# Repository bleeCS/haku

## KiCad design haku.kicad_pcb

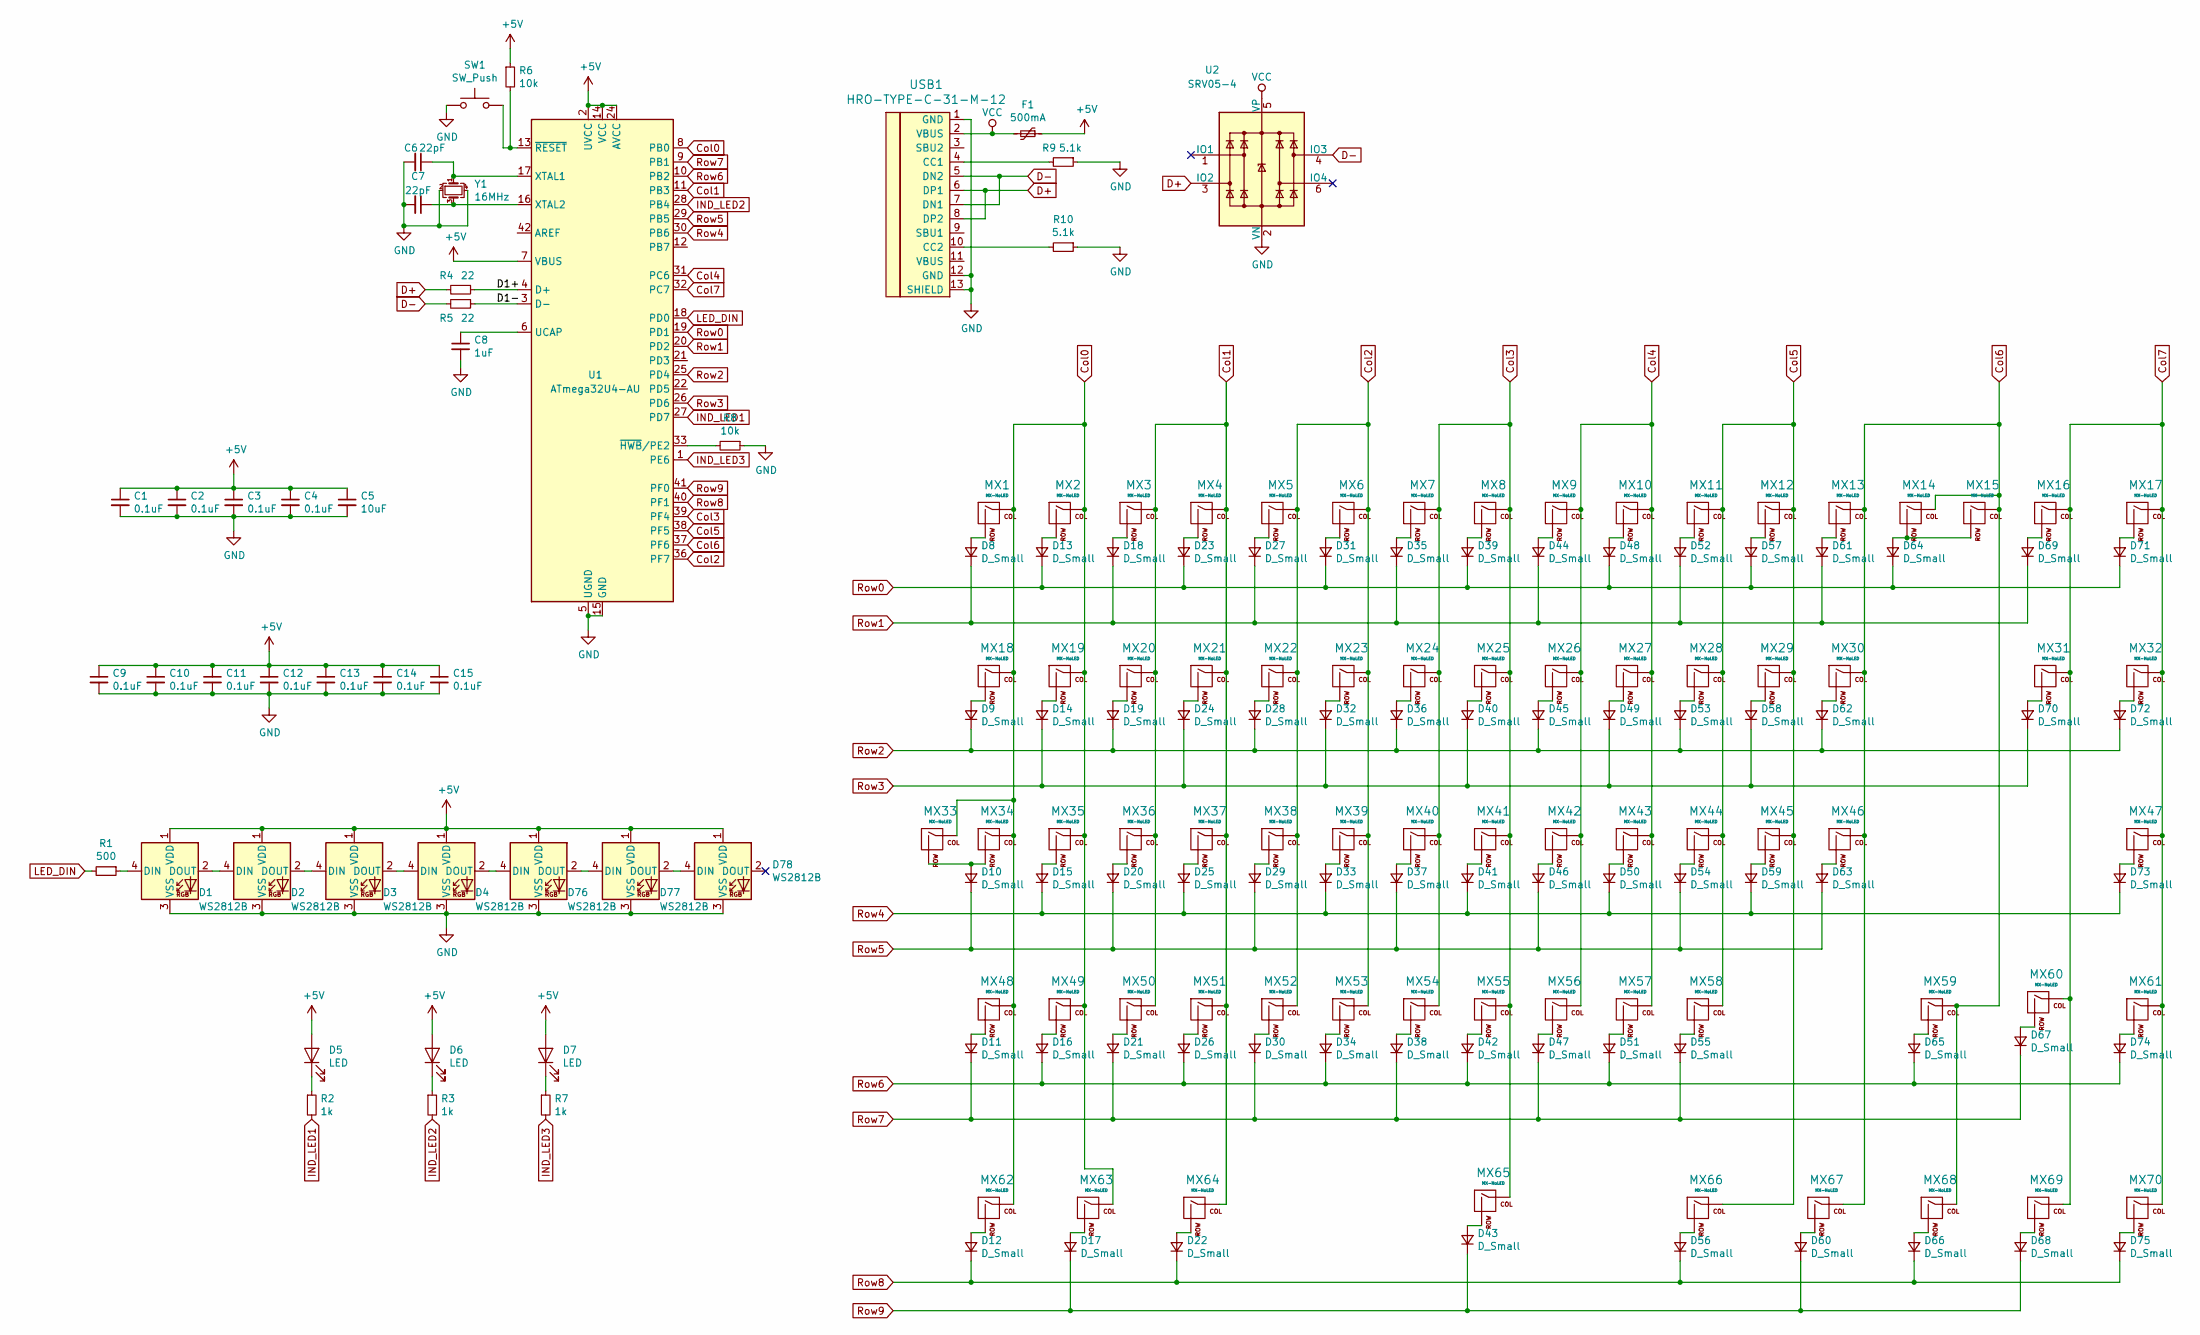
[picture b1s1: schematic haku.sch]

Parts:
C1, C2, C3, C4, C9, C10, C11, C12, C13, C14, C15: 0.1uF; C_0805_2012Metric
C5: 10uF; C_0805_2012Metric
C6, C7: 22pF; C_0805_2012Metric
C8: 1uF; C_0805_2012Metric
D1, D2, D3, D4, D76, D77, D78: WS2812B; LED_WS2812B_PLCC4_5.0x5.0mm_P3.2mm
D5, D6, D7: LED; LED_D3.0mm-Pretty
D8, D9, D10, D11, D12, D13, D14, D15, D16, D17, D18, D19, D20, D21, D22, D23, D24, D25, D26, D27, D28, D29, D30, D31, D32, D33, D34, D35, D36, D37, D38, D39, D40, D41, D42, D43, D44, D45, D46, D47, D48, D49, D50, D51, D52, D53, D54, D55, D56, D57, D58, D59, D60, D61, D62, D63, D64, D65, D66, D67, D68, D69, D70, D71, D72, D73, D74, D75: D_Small; D_SOD-123
F1: 500mA; Fuse_1206_3216Metric
MX1, MX2, MX3, MX4, MX5, MX6, MX7, MX8, MX9, MX10, MX11, MX12, MX13, MX14, MX16, MX17, MX19, MX20, MX21, MX22, MX23, MX24, MX25, MX26, MX27, MX28, MX29, MX30, MX32, MX35, MX36, MX37, MX38, MX39, MX40, MX41, MX42, MX43, MX44, MX45, MX47, MX49, MX50, MX51, MX52, MX53, MX54, MX55, MX56, MX57, MX58, MX60, MX61, MX63, MX68, MX69, MX70: MX-NoLED; MXOnly-1U-NoLED
MX15: MX-NoLED; MXOnly-2U-NoLED
MX18, MX31, MX62, MX64, MX66, MX67: MX-NoLED; MXOnly-1.5U-NoLED
MX33: MX-NoLED; MXOnly-1.25U-NoLED
MX34: MX-NoLED; MXOnly-1.75U-NoLED
MX46, MX48: MX-NoLED; MXOnly-2.25U-NoLED
MX59: MX-NoLED; MXOnly-2.75U-NoLED
MX65: MX-NoLED; MXOnly-7U-ReversedStabilizers-NoLED
R1: 500; R_0805_2012Metric
R2, R3, R7: 1k; R_0805_2012Metric
R4, R5: 22; R_0805_2012Metric
R6, R8: 10k; R_0805_2012Metric
R9, R10: 5.1k; R_0805_2012Metric
SW1: SW_Push; SKQG-1155865
U1: ATmega32U4-AU; TQFP-44_10x10mm_P0.8mm
U2: SRV05-4; SOT-23-6
USB1: HRO-TYPE-C-31-M-12; HRO-TYPE-C-31-M-12-HandSoldering
Y1: 16MHz; Crystal_SMD_3225-4Pin_3.2x2.5mm

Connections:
+5V: C1.1, C2.1, C3.1, C4.1, C5.1, C9.1, C10.1, C11.1, C12.1, C13.1, C14.1, C15.1, D1.1 (VDD), D2.1 (VDD), D3.1 (VDD), D4.1 (VDD), D5.2 (A), D6.2 (A), D7.2 (A), D76.1 (VDD), D77.1 (VDD), D78.1 (VDD), F1.1, R6.1, U1.2 (UVCC), U1.7 (VBUS), U1.14 (VCC), U1.24 (AVCC), U1.34 (VCC), U1.44 (AVCC)
/D1+: R4.1, U1.4 (D+)
/D1-: R5.1, U1.3 (D-)
Col0: MX1.1 (COL), MX2.1 (COL), MX18.1 (COL), MX19.1 (COL), MX33.1 (COL), MX34.1 (COL), MX35.1 (COL), MX48.1 (COL), MX49.1 (COL), MX62.1 (COL), MX63.1 (COL), U1.8 (PB0)
Col1: MX3.1 (COL), MX4.1 (COL), MX20.1 (COL), MX21.1 (COL), MX36.1 (COL), MX37.1 (COL), MX50.1 (COL), MX51.1 (COL), MX64.1 (COL), U1.11 (PB3)
Col2: MX5.1 (COL), MX6.1 (COL), MX22.1 (COL), MX23.1 (COL), MX38.1 (COL), MX39.1 (COL), MX52.1 (COL), MX53.1 (COL), U1.36 (PF7)
Col3: MX7.1 (COL), MX8.1 (COL), MX24.1 (COL), MX25.1 (COL), MX40.1 (COL), MX41.1 (COL), MX54.1 (COL), MX55.1 (COL), MX65.1 (COL), U1.39 (PF4)
Col4: MX9.1 (COL), MX10.1 (COL), MX26.1 (COL), MX27.1 (COL), MX42.1 (COL), MX43.1 (COL), MX56.1 (COL), MX57.1 (COL), U1.31 (PC6)
Col5: MX11.1 (COL), MX12.1 (COL), MX28.1 (COL), MX29.1 (COL), MX44.1 (COL), MX45.1 (COL), MX58.1 (COL), MX66.1 (COL), U1.38 (PF5)
Col6: MX13.1 (COL), MX14.1 (COL), MX15.1 (COL), MX30.1 (COL), MX46.1 (COL), MX59.1 (COL), MX67.1 (COL), MX68.1 (COL), U1.37 (PF6)
Col7: MX16.1 (COL), MX17.1 (COL), MX31.1 (COL), MX32.1 (COL), MX47.1 (COL), MX60.1 (COL), MX61.1 (COL), MX69.1 (COL), MX70.1 (COL), U1.32 (PC7)
D+: R4.2, U2.3 (IO2), USB1.6 (DP1), USB1.8 (DP2)
D-: R5.2, U2.4 (IO3), USB1.5 (DN2), USB1.7 (DN1)
GND: C1.2, C2.2, C3.2, C4.2, C5.2, C6.2, C7.2, C8.2, C9.2, C10.2, C11.2, C12.2, C13.2, C14.2, C15.2, D1.3 (VSS), D2.3 (VSS), D3.3 (VSS), D4.3 (VSS), D76.3 (VSS), D77.3 (VSS), D78.3 (VSS), R8.1, R9.1, R10.1, SW1.1, U1.5 (UGND), U1.15 (GND), U1.23 (GND), U1.35 (GND), U1.43 (GND), U2.2 (VN), USB1.1 (GND), USB1.12 (GND), USB1.13 (SHIELD), Y1.2, Y1.4
IND_LED1: R2.2, U1.27 (PD7)
IND_LED2: R3.2, U1.28 (PB4)
IND_LED3: R7.2, U1.1 (PE6)
LED_DIN: R1.2, U1.18 (PD0)
unnamed: C6.1, U1.17 (XTAL1), Y1.1
unnamed: C7.1, U1.16 (XTAL2), Y1.3
unnamed: C8.1, U1.6 (UCAP)
unnamed: D1.2 (DOUT), D2.4 (DIN)
unnamed: D1.4 (DIN), R1.1
unnamed: D2.2 (DOUT), D3.4 (DIN)
unnamed: D3.2 (DOUT), D4.4 (DIN)
unnamed: D4.2 (DOUT), D76.4 (DIN)
unnamed: D5.1 (K), R2.1
unnamed: D6.1 (K), R3.1
unnamed: D7.1 (K), R7.1
unnamed: D8.2 (A), MX1.2 (ROW)
unnamed: D9.2 (A), MX18.2 (ROW)
unnamed: D10.2 (A), MX33.2 (ROW), MX34.2 (ROW)
unnamed: D11.2 (A), MX48.2 (ROW)
unnamed: D12.2 (A), MX62.2 (ROW)
unnamed: D13.2 (A), MX2.2 (ROW)
unnamed: D14.2 (A), MX19.2 (ROW)
unnamed: D15.2 (A), MX35.2 (ROW)
unnamed: D16.2 (A), MX49.2 (ROW)
unnamed: D17.2 (A), MX63.2 (ROW)
unnamed: D18.2 (A), MX3.2 (ROW)
unnamed: D19.2 (A), MX20.2 (ROW)
unnamed: D20.2 (A), MX36.2 (ROW)
unnamed: D21.2 (A), MX50.2 (ROW)
unnamed: D22.2 (A), MX64.2 (ROW)
unnamed: D23.2 (A), MX4.2 (ROW)
unnamed: D24.2 (A), MX21.2 (ROW)
unnamed: D25.2 (A), MX37.2 (ROW)
unnamed: D26.2 (A), MX51.2 (ROW)
unnamed: D27.2 (A), MX5.2 (ROW)
unnamed: D28.2 (A), MX22.2 (ROW)
unnamed: D29.2 (A), MX38.2 (ROW)
unnamed: D30.2 (A), MX52.2 (ROW)
unnamed: D31.2 (A), MX6.2 (ROW)
unnamed: D32.2 (A), MX23.2 (ROW)
unnamed: D33.2 (A), MX39.2 (ROW)
unnamed: D34.2 (A), MX53.2 (ROW)
unnamed: D35.2 (A), MX7.2 (ROW)
unnamed: D36.2 (A), MX24.2 (ROW)
unnamed: D37.2 (A), MX40.2 (ROW)
unnamed: D38.2 (A), MX54.2 (ROW)
unnamed: D39.2 (A), MX8.2 (ROW)
unnamed: D40.2 (A), MX25.2 (ROW)
unnamed: D41.2 (A), MX41.2 (ROW)
unnamed: D42.2 (A), MX55.2 (ROW)
unnamed: D43.2 (A), MX65.2 (ROW)
unnamed: D44.2 (A), MX9.2 (ROW)
unnamed: D45.2 (A), MX26.2 (ROW)
unnamed: D46.2 (A), MX42.2 (ROW)
unnamed: D47.2 (A), MX56.2 (ROW)
unnamed: D48.2 (A), MX10.2 (ROW)
unnamed: D49.2 (A), MX27.2 (ROW)
unnamed: D50.2 (A), MX43.2 (ROW)
unnamed: D51.2 (A), MX57.2 (ROW)
unnamed: D52.2 (A), MX11.2 (ROW)
unnamed: D53.2 (A), MX28.2 (ROW)
unnamed: D54.2 (A), MX44.2 (ROW)
unnamed: D55.2 (A), MX58.2 (ROW)
unnamed: D56.2 (A), MX66.2 (ROW)
unnamed: D57.2 (A), MX12.2 (ROW)
unnamed: D58.2 (A), MX29.2 (ROW)
unnamed: D59.2 (A), MX45.2 (ROW)
unnamed: D60.2 (A), MX67.2 (ROW)
unnamed: D61.2 (A), MX13.2 (ROW)
unnamed: D62.2 (A), MX30.2 (ROW)
unnamed: D63.2 (A), MX46.2 (ROW)
unnamed: D64.2 (A), MX14.2 (ROW), MX15.2 (ROW)
unnamed: D65.2 (A), MX59.2 (ROW)
unnamed: D66.2 (A), MX68.2 (ROW)
unnamed: D67.2 (A), MX60.2 (ROW)
unnamed: D68.2 (A), MX69.2 (ROW)
unnamed: D69.2 (A), MX16.2 (ROW)
unnamed: D70.2 (A), MX31.2 (ROW)
unnamed: D71.2 (A), MX17.2 (ROW)
unnamed: D72.2 (A), MX32.2 (ROW)
unnamed: D73.2 (A), MX47.2 (ROW)
unnamed: D74.2 (A), MX61.2 (ROW)
unnamed: D75.2 (A), MX70.2 (ROW)
unnamed: D76.2 (DOUT), D77.4 (DIN)
unnamed: D77.2 (DOUT), D78.4 (DIN)
unnamed: R6.2, SW1.2, U1.13 (~RESET)
unnamed: R8.2, U1.33 (~HWB~/PE2)
unnamed: R9.2, USB1.4 (CC1)
unnamed: R10.2, USB1.10 (CC2)
Row0: D13.1 (K), D23.1 (K), D31.1 (K), D39.1 (K), D48.1 (K), D57.1 (K), D64.1 (K), D71.1 (K), U1.19 (PD1)
Row1: D8.1 (K), D18.1 (K), D27.1 (K), D35.1 (K), D44.1 (K), D52.1 (K), D61.1 (K), D69.1 (K), U1.20 (PD2)
Row2: D9.1 (K), D19.1 (K), D28.1 (K), D36.1 (K), D45.1 (K), D53.1 (K), D62.1 (K), D72.1 (K), U1.25 (PD4)
Row3: D14.1 (K), D24.1 (K), D32.1 (K), D40.1 (K), D49.1 (K), D58.1 (K), D70.1 (K), U1.26 (PD6)
Row4: D15.1 (K), D25.1 (K), D33.1 (K), D41.1 (K), D50.1 (K), D59.1 (K), D73.1 (K), U1.30 (PB6)
Row5: D10.1 (K), D20.1 (K), D29.1 (K), D37.1 (K), D46.1 (K), D54.1 (K), D63.1 (K), U1.29 (PB5)
Row6: D16.1 (K), D26.1 (K), D34.1 (K), D42.1 (K), D51.1 (K), D65.1 (K), D74.1 (K), U1.10 (PB2)
Row7: D11.1 (K), D21.1 (K), D30.1 (K), D38.1 (K), D47.1 (K), D55.1 (K), D67.1 (K), U1.9 (PB1)
Row8: D12.1 (K), D22.1 (K), D56.1 (K), D66.1 (K), D75.1 (K), U1.40 (PF1)
Row9: D17.1 (K), D43.1 (K), D60.1 (K), D68.1 (K), U1.41 (PF0)
VCC: F1.2, U2.5 (VP), USB1.2 (VBUS)

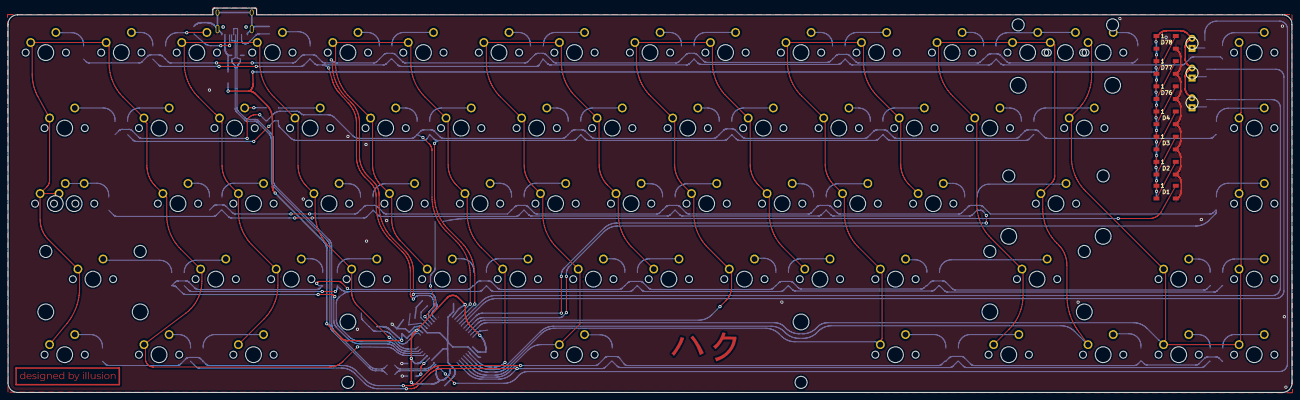
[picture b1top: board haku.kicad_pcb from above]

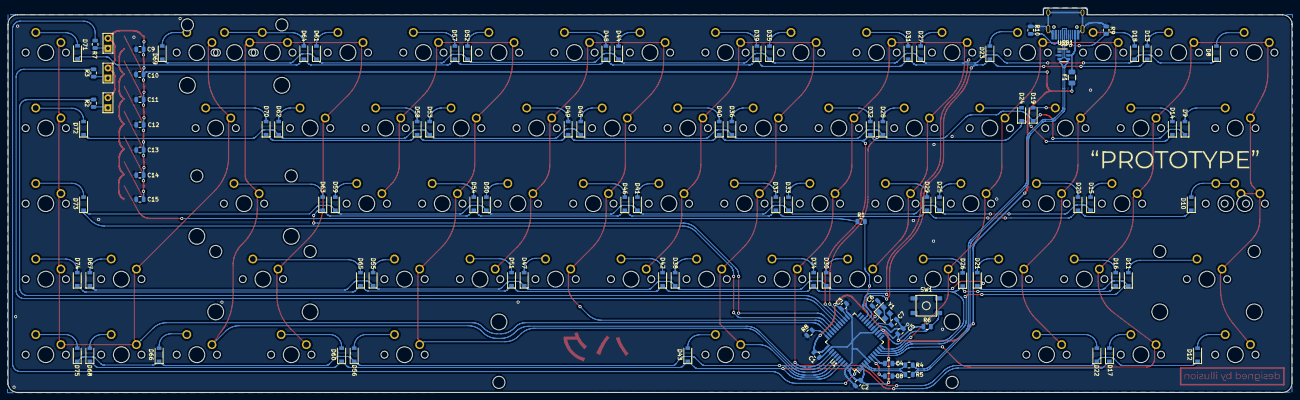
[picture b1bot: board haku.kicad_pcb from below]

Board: 2 copper layers, 323.9 x 97.0 mm, 179 parts (99 on the bottom side), 114 nets.

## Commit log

2020-03-23 initialize project
2020-03-23 add readme
2020-03-24 add submodules
2020-03-24 add symbol and footprint libs
2020-04-10 begin schematic (complete mcu, usb-c, place switches)
2020-04-11 complete indicator leds, underglow, switch matrix, ESD
2020-04-11 update switch matrix, assign footprints
2020-04-11 place components on pcb
2020-04-12 begin routing
2020-04-12 complete routing
2020-04-13 ground fills
2020-04-13 messing with silkscreen (will likely change)
2020-04-13 update data lines
2020-04-16 nudges some traces
2020-04-18 changes to traces
2020-04-18 remove silkscreen artwork, add exposed soldermask artwork
2020-04-21 move components, update traces
2020-04-21 designed by illusion
2020-04-27 lots of changes
2020-05-01 some finishing touches
2020-05-03 final changes before protos
